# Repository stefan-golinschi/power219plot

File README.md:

# power219plot

This project uses an `ina219` sensor to plot the current draw across a period of time using matplotlib.

```
conda create \
 --name power219plot \
 --yes \
 python=3.7 \
 matplotlib=3.1 \
 numpy=1.18 \
 pyserial=3.4
```

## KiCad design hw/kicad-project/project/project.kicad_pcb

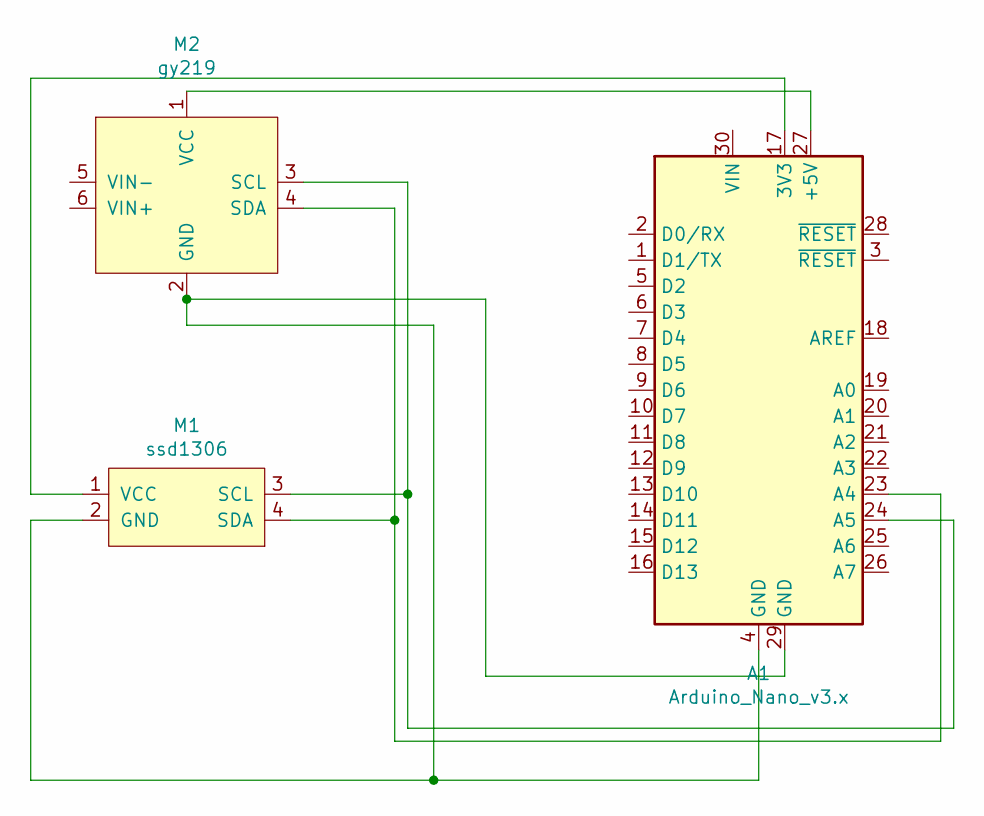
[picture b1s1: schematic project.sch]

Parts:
A1: Arduino_Nano_v3.x; Arduino_Nano
M1: ssd1306
M2: gy219; gy-219

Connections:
unnamed: A1.17 (3V3), M1.1 (VCC)
unnamed: A1.23 (A4), M1.4 (SDA), M2.4 (SDA)
unnamed: A1.24 (A5), M1.3 (SCL), M2.3 (SCL)
unnamed: A1.27 (+5V), M2.1 (VCC)
unnamed: A1.4 (GND), A1.29 (GND), M1.2 (GND), M2.2 (GND)

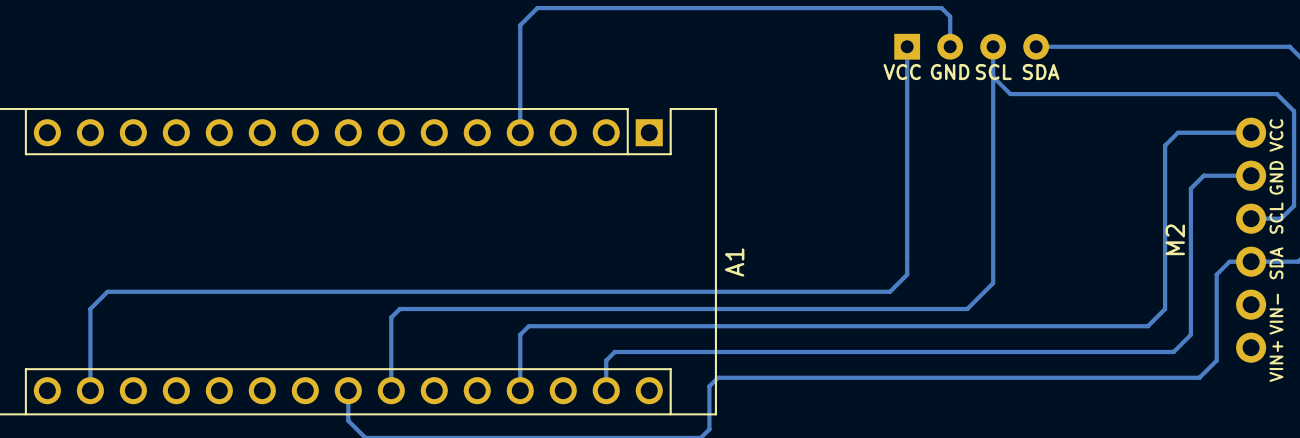
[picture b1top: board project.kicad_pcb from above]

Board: 2 copper layers, 3 parts (0 on the bottom side), 5 nets.

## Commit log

2020-06-25 created kicad project with footprints
2020-06-25 hw: round cornered pcb
2020-08-18 quick fix
